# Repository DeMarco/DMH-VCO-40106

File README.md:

# DMH-VCO-40106
 VCO module based on the design by Moritz Klein around a CD40106 Hex Inverter chip.
 I've modified the circuit considerably, but the essence is still the same:
  - Better CV processing:
      - Frequency modulation can now be attenuated completely when the amount knob is all the way CCW
      - Added trimpots to allow for fine frequency knob range adjustment and centering on a specific note (inspired by LMNC Performance VCO)
      - Added normalled connection to receive note CV directly from the Troley Bus power system
      - Added extra FM CV input (wanted to make it Linear FM instead of exponential, but gave up tryin to figure it out)
      - All CV inputs are now behind two stages of OpAmp based inverting amplifiers before hitting the transistor pair
      - Added trimpots to adjust PW knob range and symmetry, and adapted resistors to accept 100k potentiometer
  - Sync input added (so that the oscillator can be hard-synced to another)
  - Triangle wave shaper added (took from Moritz Klein Wave Folder circuit)
  - Sine wave shaper added (Thomas Henry design)
  - Tuner added (inspired by LMNC Performance VCO), my own design and firmware running on an ATtiny4313 (not Arduino)

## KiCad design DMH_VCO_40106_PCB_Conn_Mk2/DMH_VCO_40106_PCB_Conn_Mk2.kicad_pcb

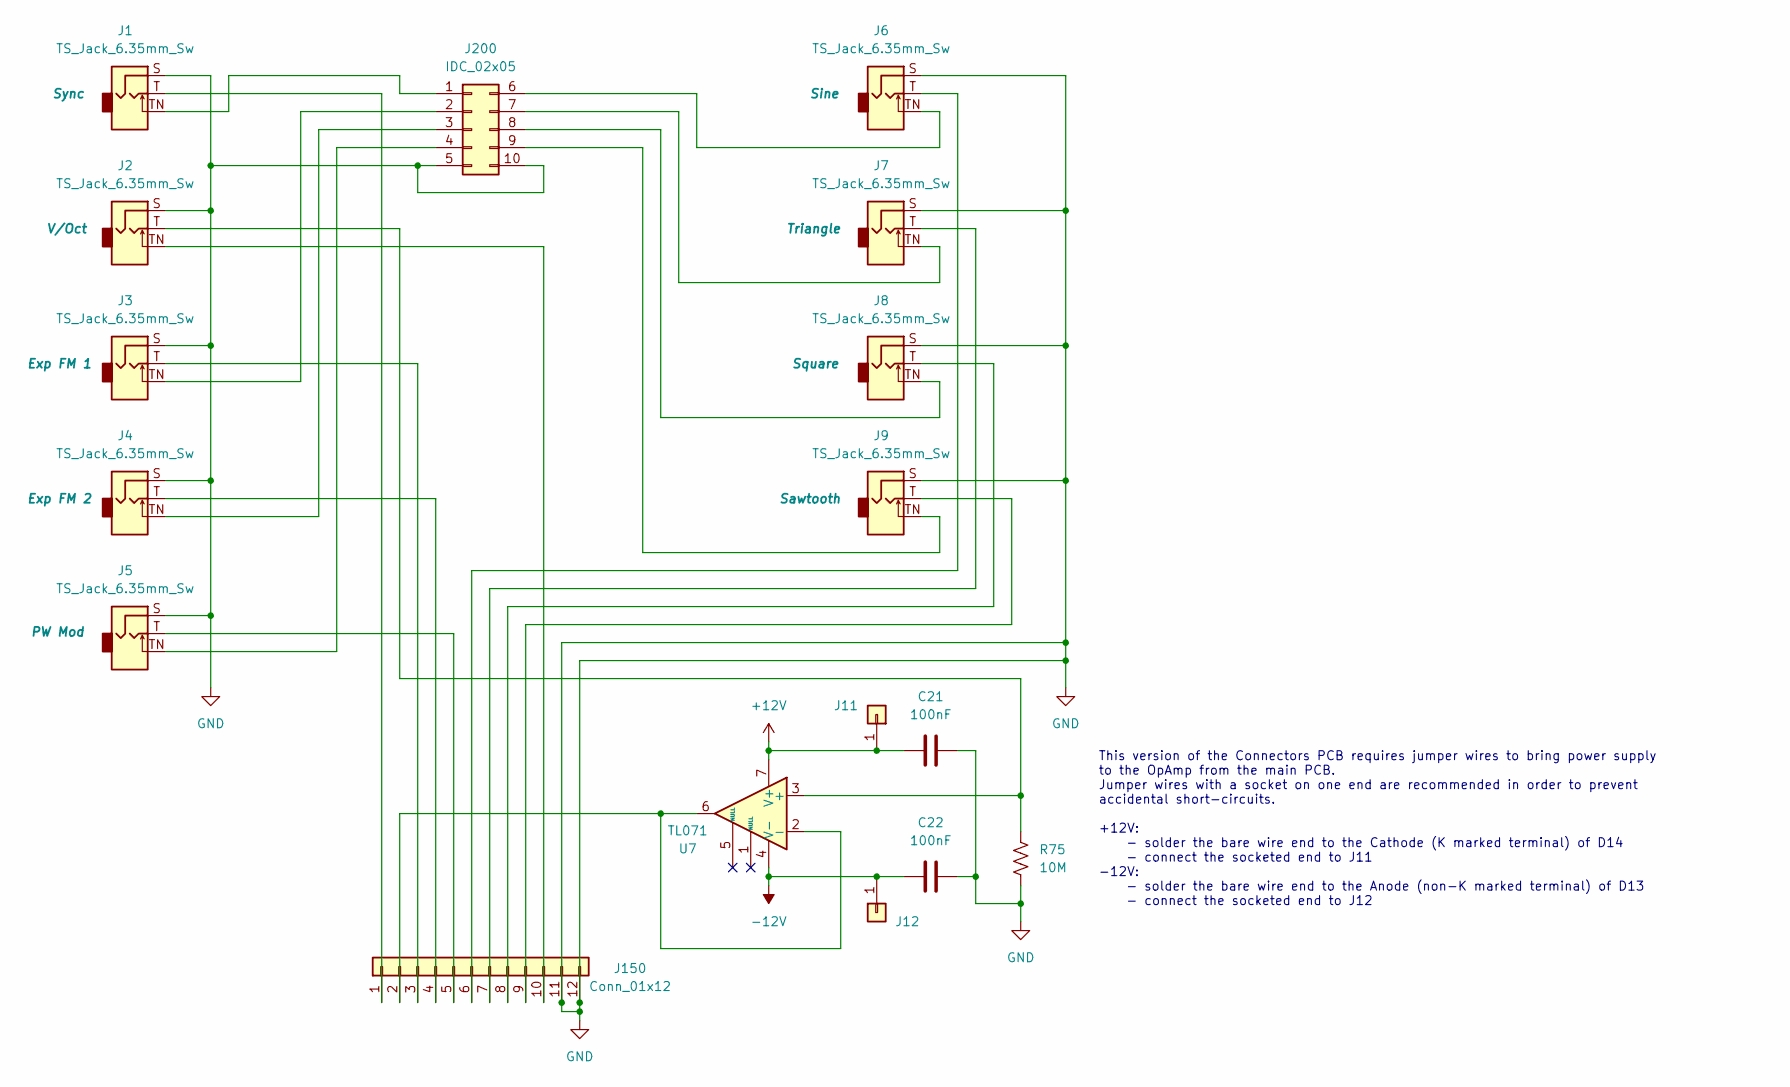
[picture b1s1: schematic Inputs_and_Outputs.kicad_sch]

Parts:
C21, C22: 100nF; C_Disc_D4.3mm_W1.9mm_P5.00mm
J1, J2, J3, J4, J5, J6, J7, J8, J9: TS_Jack_6.35mm_Sw; CUI_MJ-63052A
J11, J12: Conn_01x01; PinHeader_1x01_P2.54mm_Vertical
J150: Conn_01x12; PinHeader_1x12_P2.54mm_Vertical
J200: IDC_02x05; IDC-Header_2x05_P2.54mm_Vertical_BackBone
R75: 10M; R_Axial_DIN0207_L6.3mm_D2.5mm_P7.62mm_Horizontal
U7: TL071; DIP-8_W7.62mm_Socket

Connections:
+12V: C21.1, J11.1, U7.7 (V+)
-12V: C22.1, J12.1, U7.4 (V-)
GND: C21.2, C22.2, J1.S, J2.S, J3.S, J4.S, J5.S, J6.S, J7.S, J8.S, J9.S, J150.11, J150.12, J200.5, J200.10, R75.1
unnamed: J1.T, J150.1
unnamed: J150.2, U7.2 (-), U7.6
unnamed: J3.T, J150.3
unnamed: J4.T, J150.4
unnamed: J5.T, J150.5
unnamed: J6.T, J150.6
unnamed: J7.T, J150.7
unnamed: J8.T, J150.8
unnamed: J9.T, J150.9
unnamed: J2.TN, J150.10
unnamed: J1.TN, J200.1
unnamed: J3.TN, J200.2
unnamed: J4.TN, J200.3
unnamed: J5.TN, J200.4
unnamed: J6.TN, J200.6
unnamed: J7.TN, J200.7
unnamed: J8.TN, J200.8
unnamed: J9.TN, J200.9
unnamed: J2.T, R75.2, U7.3 (+)

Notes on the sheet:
This version of the Connectors PCB requires jumper wires to bring power supply to the OpAmp from the main PCB. Jumper wires with a socket on one end are recommended in order to prevent accidental short-circuits. +12V: - solder the bare wire end to the Cathode (K marked terminal) of D14 - connect th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

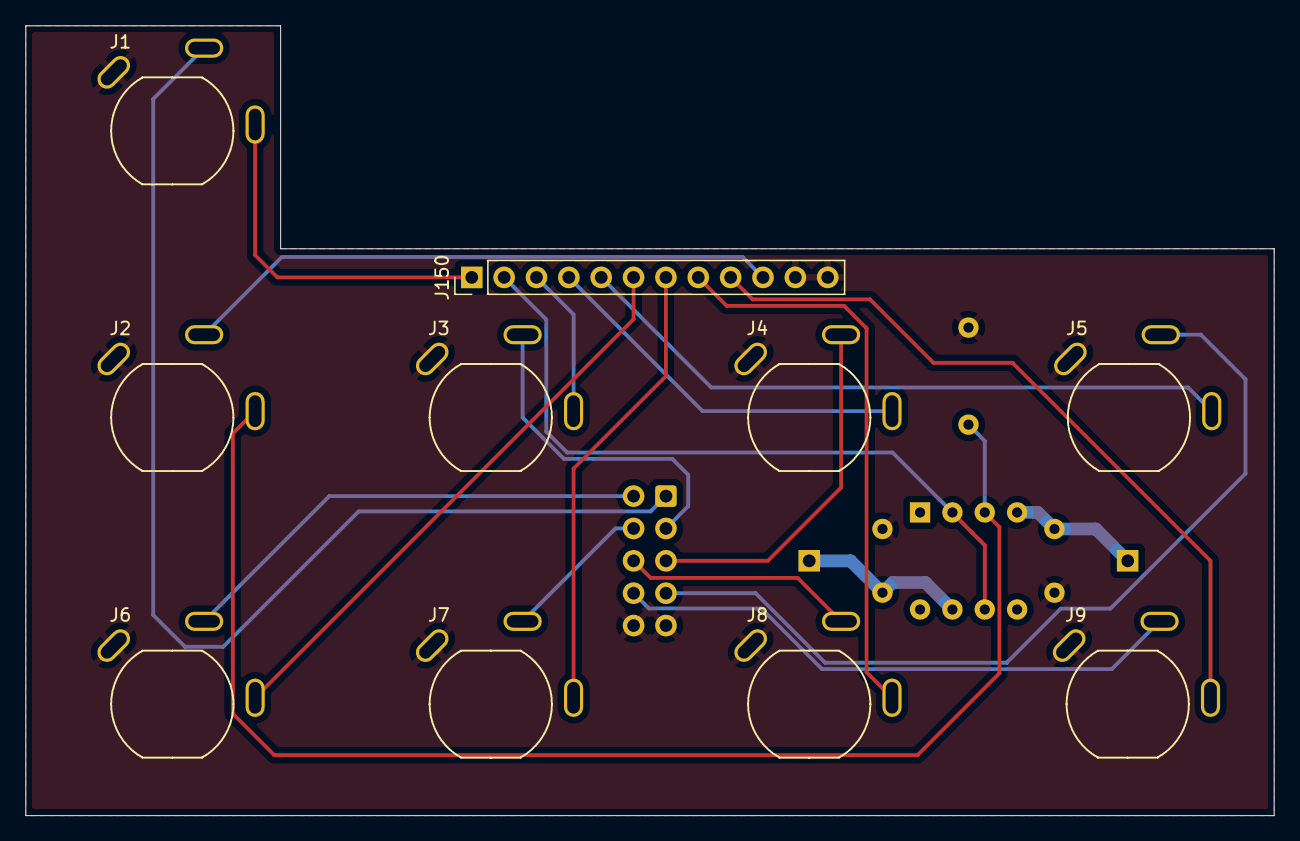
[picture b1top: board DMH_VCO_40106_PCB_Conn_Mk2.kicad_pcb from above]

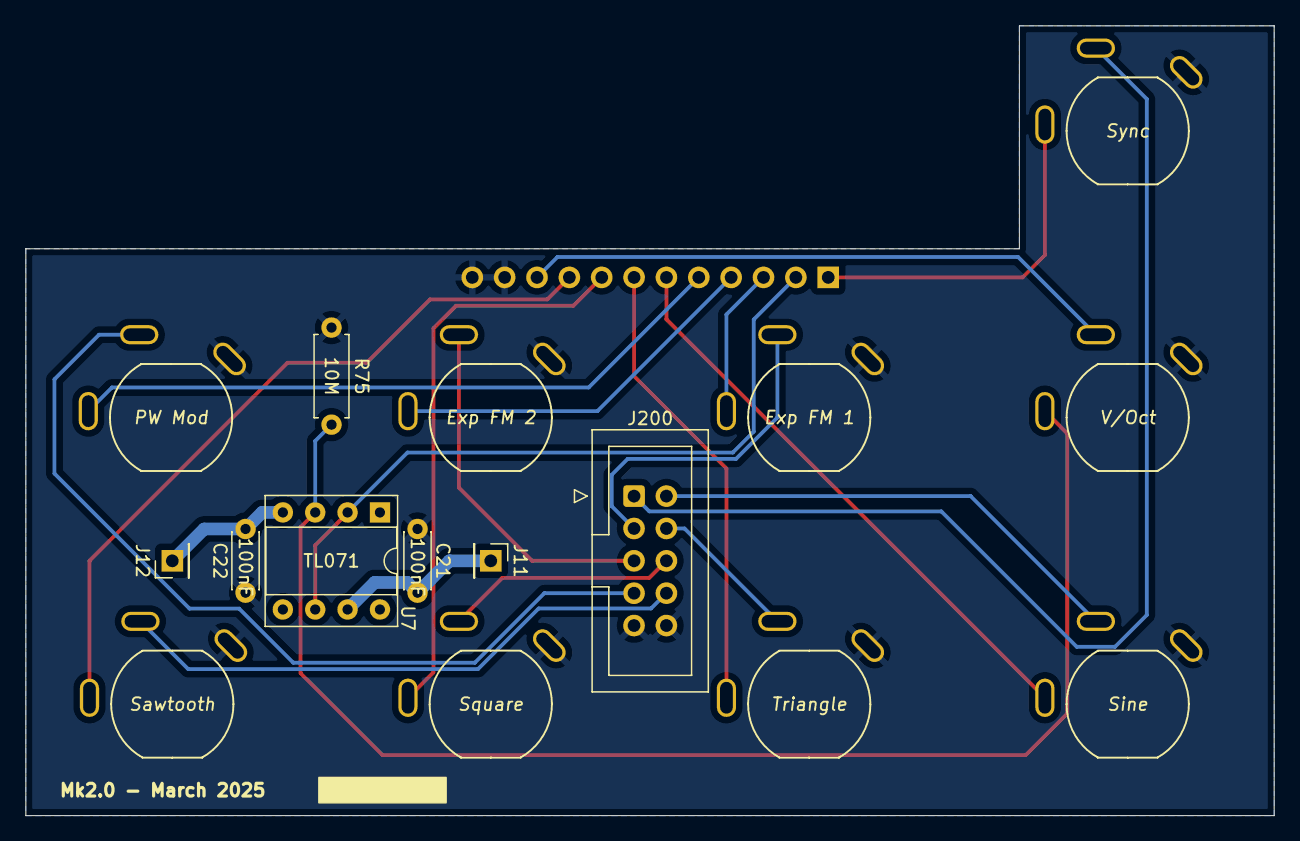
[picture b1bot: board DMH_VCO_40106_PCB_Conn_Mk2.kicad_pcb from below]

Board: 2 copper layers, 98.0 x 62.0 mm, 17 parts (7 on the bottom side), 22 nets.

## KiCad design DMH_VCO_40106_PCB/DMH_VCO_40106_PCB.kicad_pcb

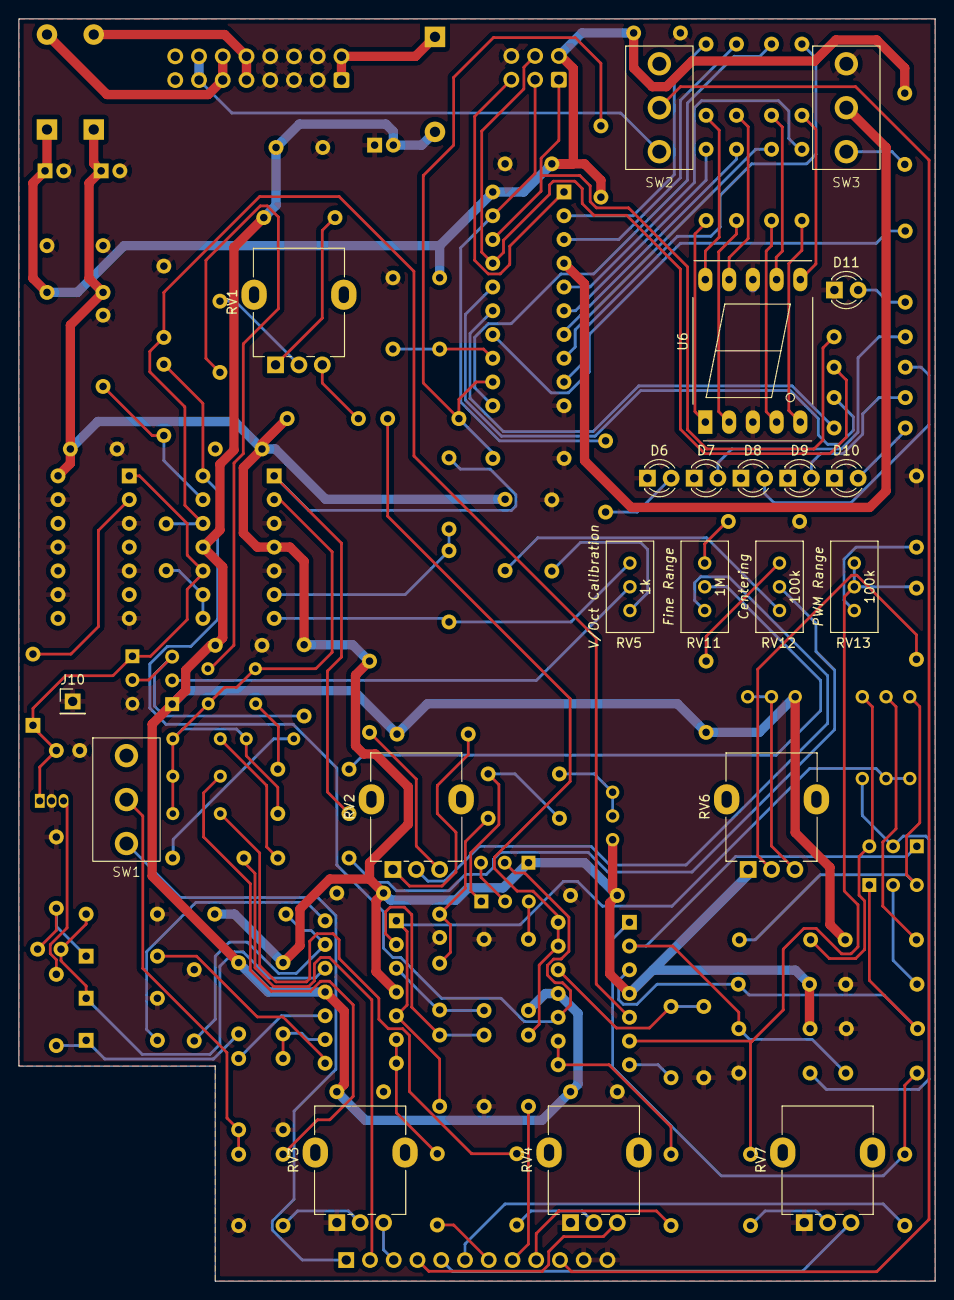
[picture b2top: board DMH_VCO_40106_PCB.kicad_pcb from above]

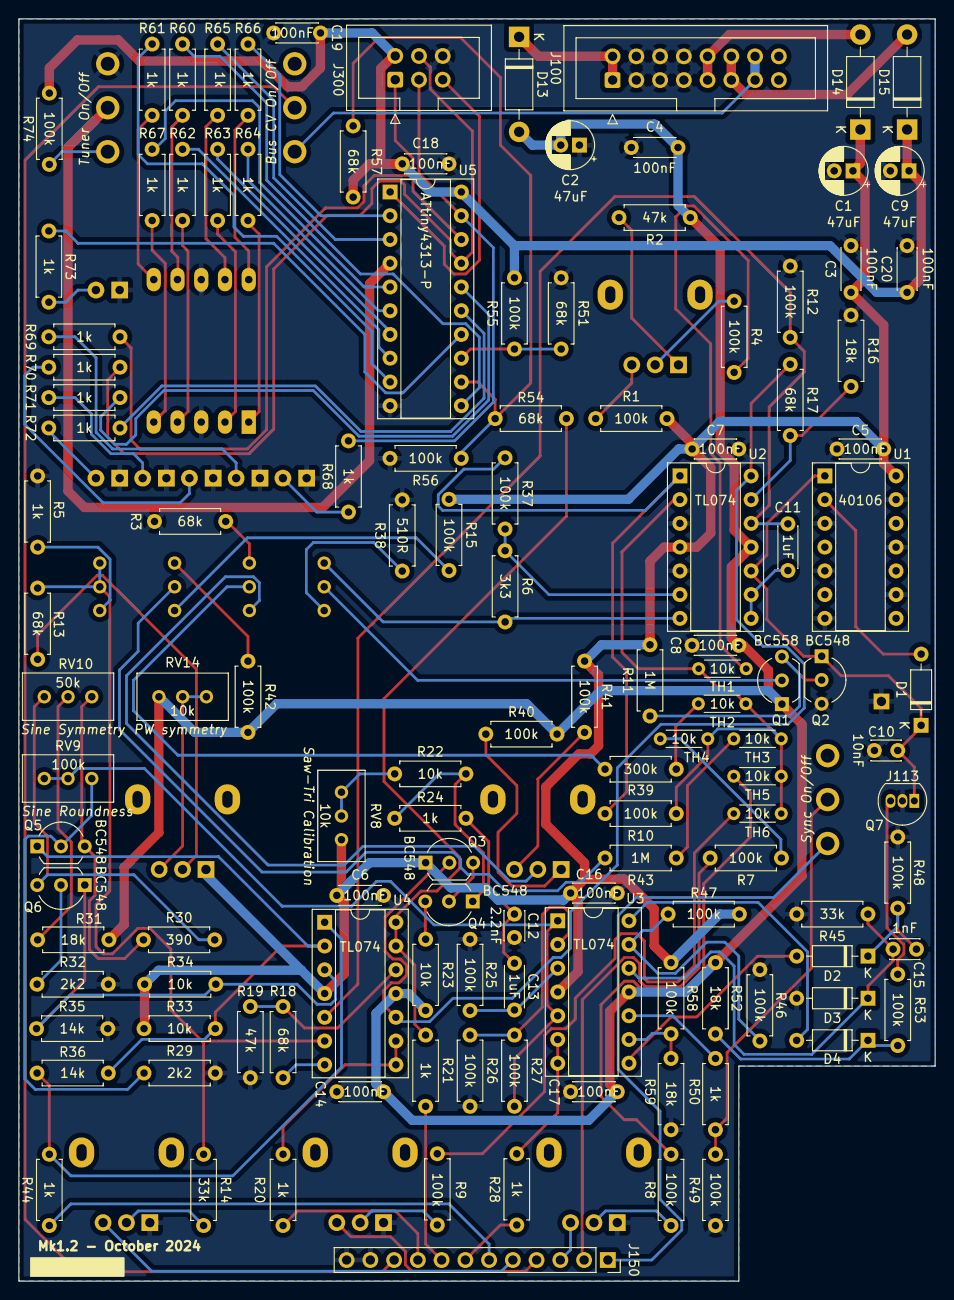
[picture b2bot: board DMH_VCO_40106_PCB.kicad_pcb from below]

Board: 2 copper layers, 98.0 x 135.0 mm, 147 parts (126 on the bottom side), 119 nets.

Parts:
C1, C2, C9: 47uF; CP_Radial_D5.0mm_P2.00mm
C3, C4, C5, C6, C7, C8, C14, C16, C17, C18, C19, C20: 100nF; C_Disc_D4.3mm_W1.9mm_P5.00mm
C10: 10nF; C_Disc_D3.0mm_W2.0mm_P2.50mm
C11, C13: 1uF; C_Disc_D4.3mm_W1.9mm_P5.00mm
C12: 2.2nF; C_Disc_D3.0mm_W2.0mm_P2.50mm
C15: 1nF; C_Disc_D3.0mm_W2.0mm_P2.50mm
D1, D2, D3, D4: 1N4148; D_DO-35_SOD27_P7.62mm_Horizontal
D6, D7, D8, D9, D10, D11: LED; LED_D3.0mm
D13: SB140-; D_DO-41_SOD81_P10.16mm_Horizontal
D14, D15: SB140+; D_DO-41_SOD81_P10.16mm_Horizontal
J10: Panel_GND; PinHeader_1x01_P2.54mm_Vertical
J100: IDC_02x08; IDC-Header_2x08_P2.54mm_Vertical_Eurorack
J150: Conn_01x12; PinSocket_1x12_P2.54mm_Vertical
J300: AVR-ISP-6; IDC-Header_2x03_P2.54mm_Vertical
Q1: BC558; TO-92_Inline_Wide
Q2, Q3, Q4, Q5, Q6: BC548; TO-92_Inline_Wide
Q7: J113; TO-92_Inline
R1, R4, R7, R8, R9, R10, R12, R15, R25, R26, R27, R37, R40, R41, R42, R46, R47, R48, R49, R53, R55, R56, R58, R74: 100k; R_Axial_DIN0207_L6.3mm_D2.5mm_P7.62mm_Horizontal
R2, R19: 47k; R_Axial_DIN0207_L6.3mm_D2.5mm_P7.62mm_Horizontal
R3, R13, R17, R18, R51, R54, R57: 68k; R_Axial_DIN0207_L6.3mm_D2.5mm_P7.62mm_Horizontal
R5, R20, R21, R24, R28, R44, R50, R60, R61, R62, R63, R64, R65, R66, R67, R68, R69, R70, R71, R72, R73: 1k; R_Axial_DIN0207_L6.3mm_D2.5mm_P7.62mm_Horizontal
R6: 3k3; R_Axial_DIN0207_L6.3mm_D2.5mm_P7.62mm_Horizontal
R11, R43: 1M; R_Axial_DIN0207_L6.3mm_D2.5mm_P7.62mm_Horizontal
R14, R45: 33k; R_Axial_DIN0207_L6.3mm_D2.5mm_P7.62mm_Horizontal
R16, R31, R52, R59: 18k; R_Axial_DIN0207_L6.3mm_D2.5mm_P7.62mm_Horizontal
R22, R23, R33, R34: 10k; R_Axial_DIN0207_L6.3mm_D2.5mm_P7.62mm_Horizontal
R29, R32: 2k2; R_Axial_DIN0207_L6.3mm_D2.5mm_P7.62mm_Horizontal
R30: 390; R_Axial_DIN0207_L6.3mm_D2.5mm_P7.62mm_Horizontal
R35, R36: 14k; R_Axial_DIN0207_L6.3mm_D2.5mm_P7.62mm_Horizontal
R38: 510R; R_Axial_DIN0207_L6.3mm_D2.5mm_P7.62mm_Horizontal
R39: 300k; R_Axial_DIN0207_L6.3mm_D2.5mm_P7.62mm_Horizontal
RV1, RV2, RV3, RV4, RV6, RV7: 100k; Potentiometer_Alpha_RD901F-40-00D_Single_Vertical
RV5: 1k; Potentiometer_Bourns_3296W_Vertical
RV8, RV14: 10k; Potentiometer_Bourns_3296W_Vertical
RV9, RV12, RV13: 100k; Potentiometer_Bourns_3296W_Vertical
RV10: 50k; Potentiometer_Bourns_3296W_Vertical
RV11: 1M; Potentiometer_Bourns_3296W_Vertical
SW1, SW2, SW3: SW_SPDT_321_OnOff; Toggle_Switch_THT
TH1, TH2, TH3, TH4, TH5, TH6: 10k; R_Axial_DIN0204_L3.6mm_D1.6mm_P5.08mm_Horizontal
U1: 40106; DIP-14_W7.62mm_Socket
U2, U3, U4: TL074; DIP-14_W7.62mm_Socket
U5: ATtiny4313-P; DIP-20_W7.62mm_Socket
U6: SM420561N; 7SegmentLED_LTS6760_LTS6780

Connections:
+5V: C9.1, C18.1, C19.1, C20.1, D15.1 (K), J300.2 (VCC), R55.2, R57.1, R74.1, U5.20 (VCC)
+12V: C1.1, C3.1, C5.1, C6.1, C7.1, C16.1, D14.1 (K), Q3.1 (C), R1.2, R11.2, R15.1, R33.1, R34.1, R41.1, R47.2, R58.1, RV6.1, RV8.1, U1.14 (VDD), U2.4 (V+), U3.4 (V+), U4.4 (V+)
-12V: C2.2, C4.2, C8.2, C14.2, C17.2, D13.2 (A), Q1.1 (C), R2.1, R23.2, R31.1, R40.2, R42.2, R52.2, RV14.3, U2.11 (V-), U3.11 (V-), U4.11 (V-)
/Core/Exp FM In 1: J150.3, RV3.3
/Core/Exp FM In 2: J150.4, RV4.3
/Core/PW Mod In: J150.5, RV7.3
/Core/Sawtooth: Q3.2 (B), R17.1, U2.14, U4.10 (+)
/Core/Sawtooth Out: J150.9, R20.2
/Core/Square: R21.1, R54.1, U4.13 (-), U4.14
/Core/Square Out: J150.8, R21.2
/Core/Sync In: R49.2, R50.2, SW1.2 (B)
/Core/V/Oct In: J150.2, R7.2
/Inpus and Outputs/Bus CV: J100.7a, J100.7b, SW2.1 (C)
/Inpus and Outputs/Sine Out Jack: J150.6, R44.1
/Inpus and Outputs/Triangle Out Jack: J150.7, R28.1
/Sine Shaper/Triangle In: R27.2, RV9.1, RV9.2, U3.1, U3.5 (+)
GND: C1.2, C2.1, C3.2, C4.1, C5.2, C6.2, C7.2, C8.1, C9.2, C10.2, C12.1, C14.1, C16.2, C17.1, C18.2, C19.2, C20.2, D3.2 (A), D6.1 (K), D7.1 (K), D8.1 (K), D9.1 (K), D10.1 (K), D11.1 (K), J10.1, J100.2a, J100.2b, J100.3a, J100.3b, J100.4a, J100.4b, J150.11, J150.12, J300.6 (GND), Q2.3 (E), Q7.2 (S), R3.1, R5.2, R12.1, R16.1, R19.2, R25.2, R26.2, R29.2, R32.2, R35.2, R38.2, R45.2, R46.1, R48.2, R49.1, R51.1, R56.2, R59.2, RV3.1, RV4.1, RV7.1, SW3.3 (A), U1.3, U1.5, U1.7 (VSS), U1.9, U1.11, U1.13, U2.3 (+), U2.5 (+), U5.10 (GND), U6.3 (CC), U6.8 (CC)
unnamed: C12.2, C13.1, R24.2
unnamed: D1.2 (A), U1.2
unnamed: C10.1, D1.1 (K), Q2.1 (C), Q7.1 (D), U1.1, U2.10 (+)
unnamed: D2.2 (A), U3.8
unnamed: C15.1, D2.1 (K), R48.1
unnamed: C15.2, D3.1 (K), R45.1, U3.12 (+)
unnamed: D4.2 (A), U3.14
unnamed: D4.1 (K), R52.1, R53.2
unnamed: D6.2 (A), R68.2
unnamed: D7.2 (A), R69.2
unnamed: D8.2 (A), R70.2
unnamed: D9.2 (A), R71.2
unnamed: D10.2 (A), R72.2
unnamed: D11.2 (A), R73.2
unnamed: D13.1 (K), J100.1a, J100.1b
unnamed: D14.2 (A), J100.5a, J100.5b
unnamed: D15.2 (A), J100.6a, J100.6b
unnamed: J150.1, SW1.1 (C)
unnamed: J150.10, SW2.2 (B)
unnamed: J300.1 (MISO), R69.1, U5.18 (PB6)
unnamed: J300.4 (MOSI), R70.1, U5.17 (PB5)
unnamed: J300.3 (SCK), R68.1, U5.19 (PB7)
unnamed: J300.5 (~RST), U5.1 (PA2/~RESET)
unnamed: Q1.2 (B), RV5.2
unnamed: Q1.3 (E), Q2.2 (B), R11.1
unnamed: Q3.3 (E), Q4.2 (B)
unnamed: Q4.1 (C), R22.2, R24.1
unnamed: Q4.3 (E), R23.1
unnamed: Q5.2 (B), R29.1, RV9.3
unnamed: Q5.1 (C), R33.2, R36.1, U4.2 (-)
unnamed: Q5.3 (E), R30.1, RV10.3
unnamed: Q6.2 (B), R32.1
unnamed: Q6.1 (C), R34.2, R35.1, U4.3 (+)
unnamed: Q6.3 (E), R30.2, RV10.1
unnamed: Q7.3 (G), R53.1
unnamed: R1.1, RV1.3
unnamed: R2.2, RV1.1
unnamed: R3.2, RV11.1
unnamed: R4.1, RV1.2
unnamed: R4.2, TH1.1
unnamed: R5.1, RV13.3
unnamed: R6.2, RV5.1, U2.7
unnamed: R7.1, TH4.1
unnamed: R8.1, RV3.2
unnamed: R8.2, TH5.1
unnamed: R9.1, RV4.2
unnamed: R9.2, TH6.1
unnamed: R10.2, R37.1, U2.1
unnamed: R13.2, RV6.2
unnamed: R14.2, RV7.2
unnamed: R15.2, RV12.3
unnamed: R18.2, U4.7
unnamed: R22.1, RV8.2, RV8.3
unnamed: R31.2, RV10.2
unnamed: R36.2, R44.2, U4.1
unnamed: R38.1, RV5.3
unnamed: R39.1, RV11.2
unnamed: R39.2, TH2.1
unnamed: R40.1, RV2.1
unnamed: R41.2, RV2.3
unnamed: R42.1, RV12.1
unnamed: R43.1, TH3.1
unnamed: R43.2, RV12.2
unnamed: RV2.2, RV11.3
unnamed: RV6.3, RV14.1, RV14.2
unnamed: SW3.2 (B), U5.4 (PA1/XTAL2)
unnamed: R74.2, SW3.1 (C)
unnamed: R10.1, TH1.2, TH2.2, TH3.2, TH4.2, TH5.2, TH6.2, U2.2 (-)
unnamed: R6.1, R37.2, U2.6 (-)
unnamed: C11.1, U2.8, U2.9 (-)
unnamed: C11.2, R12.2, U2.12 (+), U4.5 (+)
unnamed: R16.2, R17.2, U2.13 (-)
unnamed: C13.2, R25.1, U3.3 (+)
unnamed: R26.1, R27.1, U3.2 (-)
unnamed: R28.2, U3.6 (-), U3.7
unnamed: R50.1, U3.10 (+)
unnamed: R58.2, R59.1, U3.9 (-)
unnamed: R46.2, R47.1, U3.13 (-)
unnamed: R13.1, R14.1, RV13.1, RV13.2, U4.6 (-)
unnamed: R20.1, U4.8, U4.9 (-)
unnamed: R18.1, R19.1, U4.12 (+)
unnamed: R67.1, U5.5 (PA0/XTAL1)
unnamed: R54.2, R56.1, R57.2, U5.12 (PB0)
unnamed: R51.2, R55.1, U5.13 (PB1)
unnamed: R73.1, U5.14 (PB2)
unnamed: R72.1, U5.15 (PB3)
unnamed: R71.1, U5.16 (PB4)
unnamed: R66.1, U5.2 (PD0)
unnamed: R65.1, U5.3 (PD1)
unnamed: R64.1, U5.6 (PD2)
unnamed: R63.1, U5.7 (PD3)
unnamed: R62.1, U5.8 (PD4)
unnamed: R61.1, U5.9 (PD5)
unnamed: R60.1, U5.11 (PD6)
unnamed: R60.2, U6.7 (A)
unnamed: R61.2, U6.6 (B)
unnamed: R62.2, U6.4 (C)
unnamed: R63.2, U6.2 (D)
unnamed: R67.2, U6.5 (DP)
unnamed: R64.2, U6.1 (E)
unnamed: R65.2, U6.9 (F)
unnamed: R66.2, U6.10 (G)

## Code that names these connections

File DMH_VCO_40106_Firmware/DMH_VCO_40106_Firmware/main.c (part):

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		OSCCAL = better_calib_value;
	}
	
	// Set PA0 as output
	DDRA |= _BV(PORTA0);
	
	// Set PA1 as input
	DDRA &= ~_BV(PORTA1);
	
	// Activate the PA1 pull-up resistor
	PORTA |= _BV(PORTA1);
	
	// Set PB2 to PB7 ports as output, and PB0 and PB1 as input
	DDRB = 0xFC;
	
	// Disable PB0 and PB1 pull-up resistors, so they can be used as Analog Inputs
	PORTB &= ~_BV(PORTB0) & ~_BV(PORTB1);
	
	// Set all PD ports as output
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
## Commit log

2024-06-27 Moved VCO mki to its own repo
2024-06-27 Update footprints sheetfile
2024-06-29 sync libs
2024-06-29 Generated VCO Panel Gerbers for test
2024-06-29 Re-generated VCO panel gerbers for test
    Applied modifications as per JLCPCB capabilities
2024-06-29 Zipped gerbers
2024-07-02 Exported BoM
2024-07-07 Replaced power bus caps physical size
2024-07-13 synced libs
2024-07-16 Marked components using temporary values
2024-07-21 Updates from testing on breadboard
    - Removed Bus CV input, normalled it to V/oct input jack instead
    - Renamed Lin FM input to Exp FM In 2
    - Added annotations about temporary resistor/pot values
    - Added annotations about pots and trimpots pinout
2024-07-22 Update Core.kicad_sch
    - Inverted PW Mod pot orientation.
2024-07-27 Added Cermet 3296W fp to trimpots
2024-07-28 Changed Exp FM input attenuator circuitry
    Made it so that I can kill the modulation completely when the pot is all de way CCW.
2024-07-29 Added inverting summer to CV intake
    Design not finished, needs testing and calibration
2024-07-30 V/Oct tracking in progress
2024-08-02 Updated exponentiator resistors and capacitors
2024-08-03 Added trimpots for fine centering and range
2024-08-03 Improved fine freq adjustment
    And tidied up the CV input summing section
2024-08-03 Changed Fine Range trimpot strategy
    ... in order to allow for range adjustment from -/+13 to -/+0.5 semitones
2024-08-04 Improved PWM part
    Made PWM totally killable with 100k "amt" pot.
    Added duty cycle range trimpot.
    Added duty cycle balancing trimpot.
2024-08-04 Added thermistor to the centring trimpot line
2024-08-06 Made U3 into TL074 instead of TL072
2024-08-06 Added not about 2.2uF cap
2024-08-08 Corrected capacitor value
    Should be 2.2nF, not 2.2uF
2024-08-09 Improved range of Coarse knob
    ... and allowed Centering knob to set C1=32,7Hz as root note with Coarse knob all the way CCW.
    ... and added 1kHz to Sine output.
2024-08-10 Replaced 2N3904 with BC548
2024-08-10 Adjusted all output gains to 10Vpp
    ... and added buffer stages for Sawtooth Out and Triangle Out in order to avoid modifying Triangle and Sine wafeform characteristics when connecting Sawtooth Out and Triangle Out to other modules.
2024-08-10 Added sawtooth zero crossing pulse generator
2024-08-10 Finished Sync input design
2024-08-10 Placed power for U4
2024-08-11 Added Sync and Bus CV switches
2024-08-11 Fixed bug on sync input circuit
    ... in order to keep the pulse generator quiet when no signal is connected to the sync input.
2024-08-11 Added tuner circuit
2024-08-11 Placed unconnected flags where missing
2024-08-13 Updated Tuner
    - Changed uC to ATtiny4313
    - Added LEDs
    - Created "function" field and updated all jacks, switches and pots
2024-08-15 Organized power part and added protection diodes
2024-08-15 Prepared for backbone connections design
2024-08-16 Update SynthStuff
2024-08-16 Added normalled backbone connections
2024-08-16 Prepared Inputs/Outputs sheet to split in 2 PCBs
2024-08-16 Updated pot mounting hole sizes
2024-08-16 Fixed trimpot fp linking
2024-08-16 Updated pot mounting hole fps
2024-08-16 Started main PCB design
2024-08-18 Added panel hole references to main PCB
2024-08-18 Started positioning components on PCB
    Moving some input resistores from main PCB to Jacks PCB
2024-08-18 Component placement ongoing
2024-08-21 Placed all components in PCB
2024-08-22 Organized Square and Sine Shaper components
    Also re-annotated the TL074 ICs to improve the layout
2024-08-23 Finished physical placement
2024-08-23 Adjusted silk screen
2024-08-24 Aded silkscreen labels to jacks and pots
2024-08-24 Routed power lines
2024-08-24 Routing in progress
2024-08-24 Finished routing main PCB
2024-08-24 Limited main PCB and finished routing
2024-08-24 Created separate connectors PCB
2024-08-24 Added SynthStuff submodule library
2024-08-24 Readded SynthStuff
2024-08-24 Added pcb project separation note
2024-08-25 Created Microchip Studio project for tuner FW
2024-08-25 Definitions creation ongoing
2024-08-26 Corrected RD90 pots pin 1 and 3 connections
    Otherwise all 6 pots would behave as if inverted
2024-08-27 Updated definitions and started display function
    Defined LED on an off macros
    Defined 7 segment name macros
    Defined note name macros
2024-08-27 Removed the flat sign LED
    and rerouted segments A and B to PORTD 6 and 7 respective,
    and rerouted the DP segment to PORTA0
2024-08-27 Connected LEDs to Tuner On/off switch
2024-08-28 Placed input and output resistors back in main PCB
    This ensures a more clear schematic and leaves the Connectors PCB only with actual connectors.
2024-08-28 Created init_display and delay_s functions
2024-08-31 Connected tuner switch to uC GPIO pin
    ... and all LED and display segments directly to GND
2024-09-01 Added PORTA1 definition as OnOff_SWITCH
2024-09-01 Added all notes to display_note function
2024-09-01 Completed ioinit function
    Configured output pins, input pins, analog input pints, analog comparator and 16bit timer
2024-09-02 Added ".atsuo" file to gitignore
2024-09-04 Replaced display seg calculation with direct value
2024-09-06 Created frequency tables in program memory
2024-09-09 Added Timer0 settings to ioinit()
2024-09-11 In progress
2024-09-12 Firmware complete and ready for testing
2024-09-14 Added facilities to flash the firmware
2024-09-14 Improved ioinit and display init
2024-09-14 Fixed mistake with too low note segment pattern
    ... and added default case for diagnostics
2024-09-14 FW work in progress
    Code left in state where fixed frequency point (e.g. 300Hz) is recognized, and the tuner swings from TOO LOW to TOO HIGH depending if below or above this frequency. I see a ~+10Hz offset though if ch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
2024-09-15 Updated PCB with rerouting of square wave to tuner
2024-09-15 Added pull up resistor to tuner switch
2024-09-15 Working state but with freq offset issue
2024-09-15 Added EESAVE fuse to flash_fuses.bat
2024-09-16 FW working version
2024-09-16 Cleaned up FW and made better comments
2024-09-16 Prepared PCBs for fabrication
2024-09-16 Replaced JLCJLCJLCJLC with space for serial number
2024-09-22 Added 3D models to VCO
2024-09-24 Used Mounting Hole Trimpot symbol
2024-09-24 Synced with trimpot mounting hole footprint
2024-09-25 Added calib data file to gitignore
2024-09-26 RC calib via EEPROM instead of defines.h
2024-09-26 Added note about R5 value
2024-09-27 Added firmware hex output file to repo
2024-09-29 Added comments about deviations
2024-10-01 Fixed resistor values and regenerated gerbers
    New gerbers version: Mk1.2
    Includes fix with small font problem with the # sign under the blue LED on the front panel.
2024-10-20 Added comment about R42
2025-01-02 Added V/Oct input buffering to main schematic
2025-01-02 Added info about jumpers to main PCB schematic
2025-01-02 Added GND to J200
    ... which means J2, J3 and J4 connections had to change pins.
2025-01-02 Started PCB Conn Mk2 separate project
2025-01-02 Routed Mk2 conn PCB
2025-03-01 Converted to KiCad 9
2025-03-01 Changed buffer resistor to 10M
2025-03-15 Generated PCB Conn Mk2 Gerbers
2025-04-27 Updated comment about R42
2025-10-08 Updated Kicad 9
2025-12-20 KiCad 9
2026-04-03 Exported scheamtic pdf
2026-04-03 Relocated Gerbers to main folder
2026-04-03 Renamed schematics PDF
2026-04-28 Created 5cm Panel version
